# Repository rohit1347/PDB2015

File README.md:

# PDB2015
Final Power Distribution Board used by SRM Team ROBOCON for the ROBOCON 2015 competition.

Features-
- Buck voltage regulators for 5V o/p.
- Linear voltage regulators for 5V, 9V, 12V o/p.
- Diode having high forward current capacity. This diode is used for preventing back current flow caused by motors.
- MOSFETs to be used as simple switches.
- Fuses to prevent high current usage.
- XT60 connector to connect with LIPO cell.
- 2 layered PCB.
- Designed on EAGLE CAD.

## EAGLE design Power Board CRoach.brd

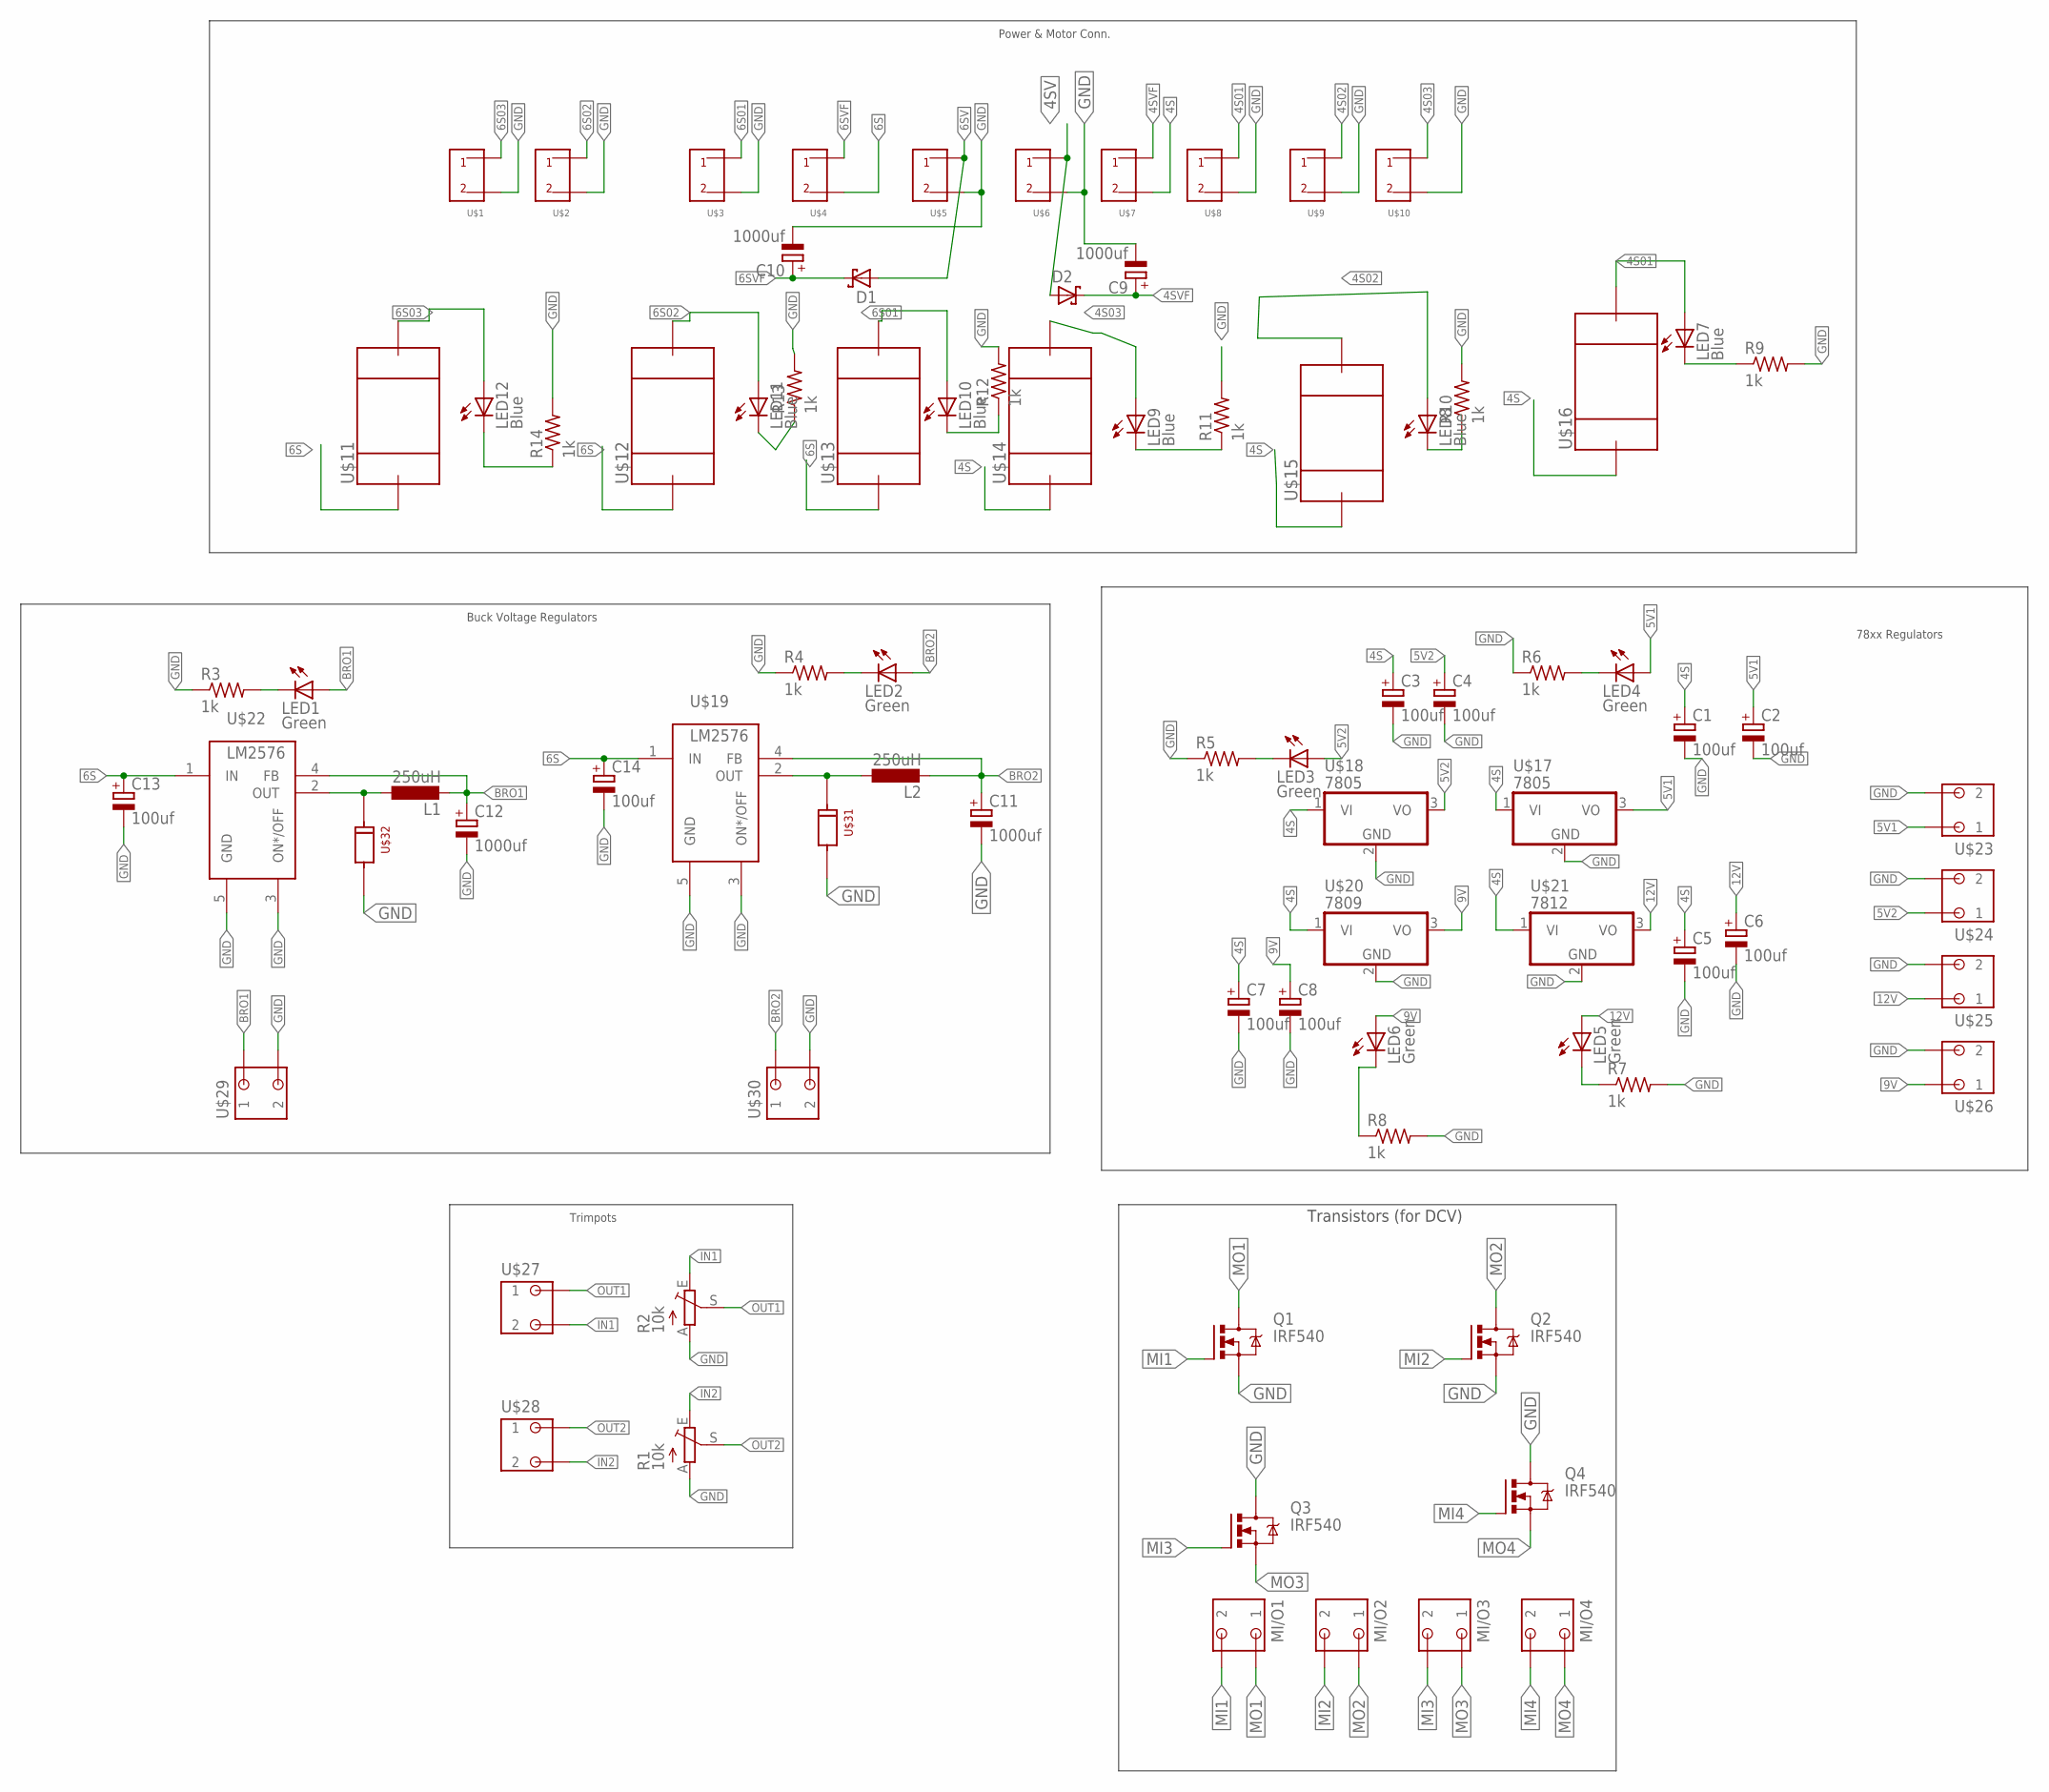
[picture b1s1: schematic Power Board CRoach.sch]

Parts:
C1, C2, C3, C4, C5, C6, C7, C8: 100uf; E2-5
C9, C10, C11, C12: 1000uf; E7,5-16
C13, C14: 100uf; E2,5-5
D1, D2: SCHOTTKY-DIODEP6T15; P6T15
L1, L2: 250uH; 0204/7
LED1, LED2, LED3, LED4, LED5, LED6: Green; LED5MM
LED7, LED8, LED9, LED10, LED11, LED12: Blue; LED5MM
MI/O1, MI/O2, MI/O3, MI/O4: SPTBB2-A2; SPTB
Q1, Q2, Q3, Q4: IRF540; TO220BV
R1, R2: 10k; CA6V
R3, R4, R5, R6, R7, R8, R9, R10, R11, R12, R13, R14: 1k; 0204/7
U$1, U$2, U$3, U$4, U$5, U$6, U$7, U$8, U$9, U$10: SCREW_XT-60
U$11, U$12, U$13, U$14, U$15, U$16: CPT-FUSE; CPT-FUSES
U$17, U$18: 7805; 78XX
U$19, U$22: LM2576
U$20: 7809; 78XX
U$21: 7812; 78XX
U$23, U$24, U$27, U$28: SPTBB2-A1; SPTB
U$25, U$26, U$29, U$30: SPTBA2-B1; SPTB
U$31, U$32: 1N5822

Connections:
4S: C1.+, C3.+, C5.+, C7.+, U$7.P$2, U$14.P$1, U$15.P$1, U$16.P$1, U$17.1 (VI), U$18.1 (VI), U$20.1 (VI), U$21.1 (VI)
4S01: LED7.A, U$8.P$1, U$16.P$2
4S02: LED8.A, U$9.P$1, U$15.P$2
4S03: LED9.A, U$10.P$1, U$14.P$2
4SV: D2.A, U$6.P$1
4SVF: C9.+, D2.C, U$7.P$1
5V1: C2.+, LED4.A, U$17.3 (VO), U$23.B2 (1)
5V2: C4.+, LED3.A, U$18.3 (VO), U$24.B2 (1)
6S: C13.+, C14.+, U$4.P$2, U$11.P$1, U$12.P$1, U$13.P$1, U$19.1 (IN), U$22.1 (IN)
6S01: LED10.A, U$3.P$1, U$13.P$2
6S02: LED11.A, U$2.P$1, U$12.P$2
6S03: LED12.A, U$1.P$1, U$11.P$2
6SV: D1.A, U$5.P$1
6SVF: C10.+, D1.C, U$4.P$1
9V: C8.+, LED6.A, U$20.3 (VO), U$26.A2 (1)
12V: C6.+, LED5.A, U$21.3 (VO), U$25.A2 (1)
BRO1: C12.+, L1.2, LED1.A, U$22.4 (FB), U$29.A2 (1)
BRO2: C11.+, L2.2, LED2.A, U$19.4 (FB), U$30.A2 (1)
GND: C1.-, C2.-, C3.-, C4.-, C5.-, C6.-, C7.-, C8.-, C9.-, C10.-, C11.-, C12.-, C13.-, C14.-, Q1.S, Q2.S, Q3.D, Q4.D, R1.A, R2.A, R3.1, R4.1, R5.1, R6.1, R7.2, R8.2, R9.2, R10.2, R11.2, R12.2, R13.2, R14.2, U$1.P$2, U$2.P$2, U$3.P$2, U$5.P$2, U$6.P$2, U$8.P$2, U$9.P$2, U$10.P$2, U$17.2 (GND), U$18.2 (GND), U$19.3 (ON*/OFF), U$19.5 (GND), U$20.2 (GND), U$21.2 (GND), U$22.3 (ON*/OFF), U$22.5 (GND), U$23.A1 (2), U$24.A1 (2), U$25.B1 (2), U$26.B1 (2), U$29.B1 (2), U$30.B1 (2), U$31.-, U$32.-
IN1: R2.E, U$27.A1 (2)
IN2: R1.E, U$28.A1 (2)
MI1: MI/O1.A2 (2), Q1.G
MI2: MI/O2.A2 (2), Q2.G
MI3: MI/O3.A2 (2), Q3.G
MI4: MI/O4.A2 (2), Q4.G
MO1: MI/O1.B2 (1), Q1.D
MO2: MI/O2.B2 (1), Q2.D
MO3: MI/O3.B2 (1), Q3.S
MO4: MI/O4.B2 (1), Q4.S
unnamed: LED7.K (C), R9.1
unnamed: LED8.K (C), R10.1
unnamed: LED9.K (C), R11.1
unnamed: LED10.K (C), R12.1
unnamed: LED11.K (C), R13.1
unnamed: LED12.K (C), R14.1
unnamed: L1.1, U$22.2 (OUT), U$32.+
unnamed: L2.1, U$19.2 (OUT), U$31.+
unnamed: LED5.K (C), R7.1
unnamed: LED6.K (C), R8.1
unnamed: LED3.K (C), R5.2
unnamed: LED4.K (C), R6.2
unnamed: LED2.K (C), R4.2
unnamed: LED1.K (C), R3.2
OUT1: R2.S, U$27.B2 (1)
OUT2: R1.S, U$28.B2 (1)

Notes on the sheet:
78xx Regulators
Trimpots
Power & Motor Conn.
Buck Voltage Regulators
Transistors (for DCV)

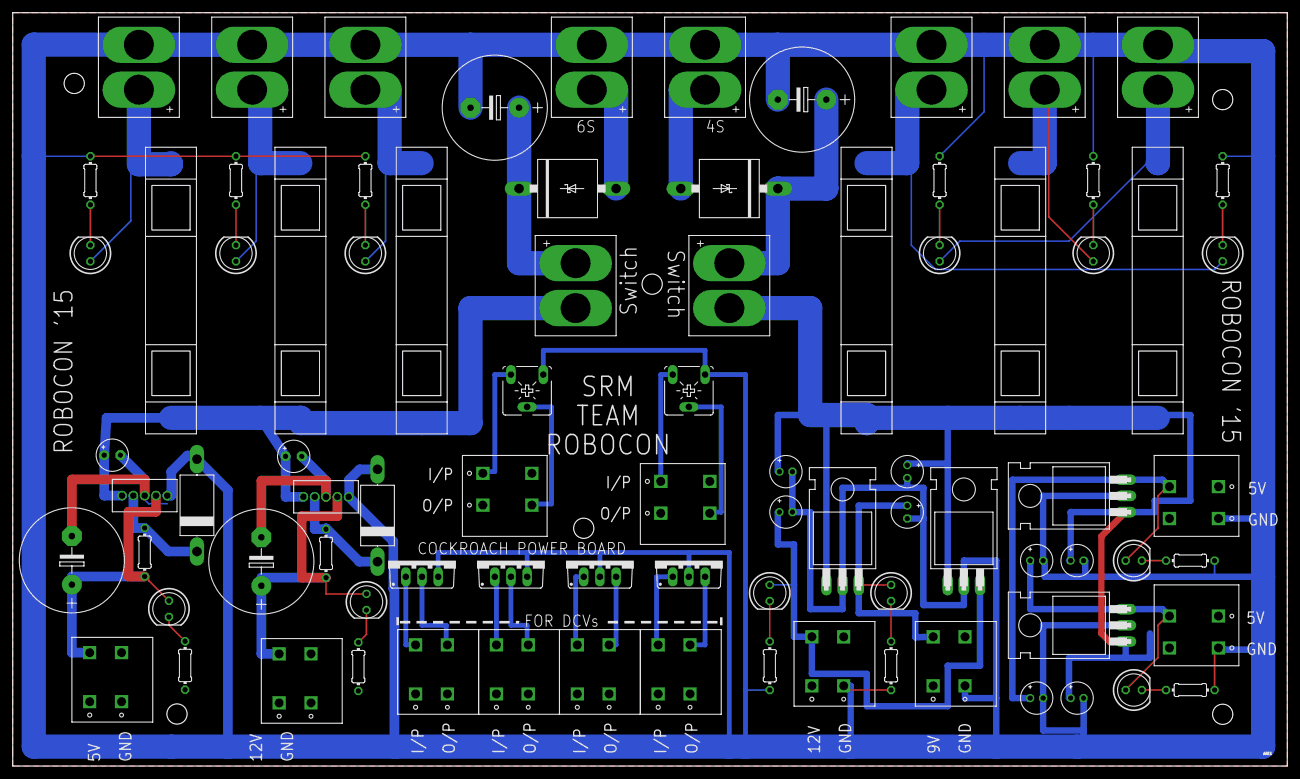
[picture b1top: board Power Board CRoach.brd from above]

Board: 2 copper layers, 200.1 x 118.3 mm, 84 parts (0 on the bottom side), 45 nets.
